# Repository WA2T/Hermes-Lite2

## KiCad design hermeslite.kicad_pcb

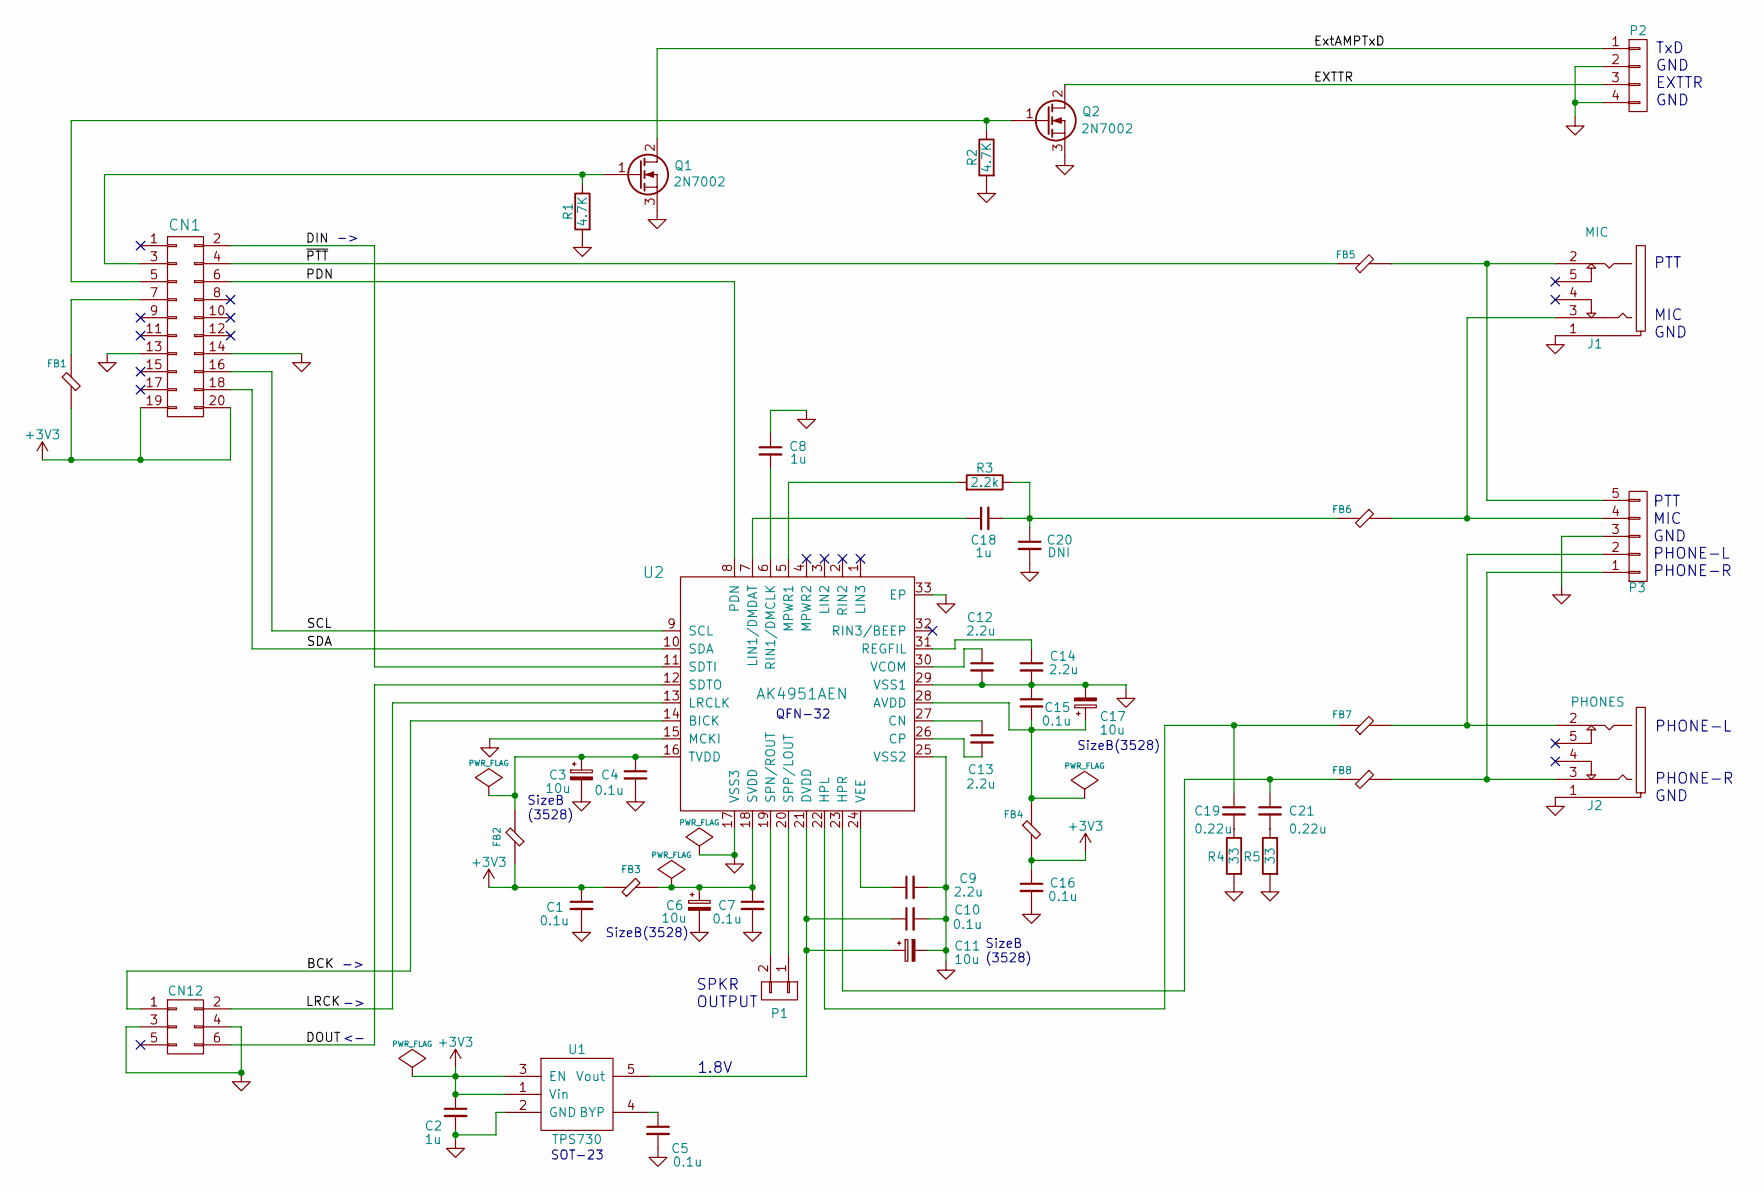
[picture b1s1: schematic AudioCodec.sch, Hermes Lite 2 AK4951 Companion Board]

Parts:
C1, C4, C5, C7, C10, C15, C16: 0.1u; SMD-0603
C2, C8, C18: 1u; SMD-0603
C3, C6, C11, C17: 10u; SMD-1206
C9, C12, C13, C14: 2.2u; SMD-0603
C19, C21: 0.22u; SMD-0603
C20: DNI; SMD-0603
CN1: IO20; 10x2
CN12: CONN_02X03; 3x2
FB1, FB2, FB3, FB4, FB5, FB6, FB7, FB8: FB; SMD-0603
J1: MIC; STEREO
J2: PHONES; STEREO
P1: CONN_01X02; 2x1
P2: CONN_01X04; 4x1
P3: CONN_01X05; 5x1
Q1, Q2: 2N7002; SOT23_2N7002
R1, R2: 4.7K; SMD-0603
R3: 2.2k; SMD-0603
R4, R5: 33; SMD-0603
U1: TPS730; SOT23
U2: AK4951AEN; QFN-32-1EP_4x4mm_Pitch0.4mm_Handsoldering

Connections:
+3V3: C1.1, C2.1, C16.1, CN1.19, CN1.20, FB1.1, FB2.2, FB3.2, FB4.1, U1.1 (Vin), U1.3 (EN)
/AudioCodec/BCK: CN12.1, U2.14 (BICK)
/AudioCodec/DIN: CN1.2, U2.11 (SDTI)
/AudioCodec/DOUT: CN12.6, U2.12 (SDTO)
/AudioCodec/EXTTR: P2.3, Q2.2 (D)
/AudioCodec/ExtAMPTxD: P2.1, Q1.2 (D)
/AudioCodec/LRCK: CN12.2, U2.13 (LRCLK)
/AudioCodec/PDN: CN1.6, U2.8 (PDN)
/AudioCodec/SCL: CN1.16, U2.9 (SCL)
/AudioCodec/SDA: CN1.18, U2.10 (SDA)
/AudioCodec/~PTT: CN1.4, FB5.2
GND: C1.2, C2.2, C3.2, C4.2, C5.2, C6.2, C7.2, C8.1, C9.2, C10.2, C11.2, C12.2, C14.2, C15.1, C16.2, C17.2, C20.2, CN1.13, CN1.14, CN12.3, CN12.4, J1.1, J2.1, P2.2, P2.4, P3.3, Q1.3 (S), Q2.3 (S), R1.2, R2.2, R4.2, R5.2, U1.2 (GND), U2.15 (MCKI), U2.17 (VSS3), U2.25 (VSS2), U2.29 (VSS1), U2.33 (EP)
unnamed: C3.1, C4.1, FB2.1, U2.16 (TVDD)
unnamed: C5.1, U1.4 (BYP)
unnamed: C6.1, C7.1, FB3.1, U2.18 (SVDD)
unnamed: C8.2, U2.6 (RIN1/DMCLK)
unnamed: C9.1, U2.24 (VEE)
unnamed: C10.1, C11.1, U1.5 (Vout), U2.21 (DVDD)
unnamed: C12.1, U2.30 (VCOM)
unnamed: C13.1, U2.27 (CN)
unnamed: C13.2, U2.26 (CP)
unnamed: C14.1, U2.31 (REGFIL)
unnamed: C15.2, C17.1, FB4.2, U2.28 (AVDD)
unnamed: C18.1, U2.7 (LIN1/DMDAT)
unnamed: C18.2, C20.1, FB6.1, R3.1
unnamed: C19.1, FB7.2, U2.22 (HPL)
unnamed: C19.2, R4.1
unnamed: C21.1, FB8.1, U2.23 (HPR)
unnamed: C21.2, R5.1
unnamed: CN1.3, Q1.1 (G), R1.1
unnamed: CN1.5, Q2.1 (G), R2.1
unnamed: CN1.7, FB1.2
unnamed: FB5.1, J1.2, P3.5
unnamed: FB6.2, J1.3, P3.4
unnamed: FB7.1, J2.2, P3.2
unnamed: FB8.2, J2.3, P3.1
unnamed: P1.1, U2.20 (SPP/LOUT)
unnamed: P1.2, U2.19 (SPN/ROUT)
unnamed: R3.2, U2.5 (MPWR1)

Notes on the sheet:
SPKR OUTPUT
PHONE-L PHONE-R GND
1.8V
PTT MIC GND PHONE-L PHONE-R
TxD GND EXTTR GND
SizeB (3528)
SizeB(3528)
SOT-23
QFN-32
PTT MIC GND

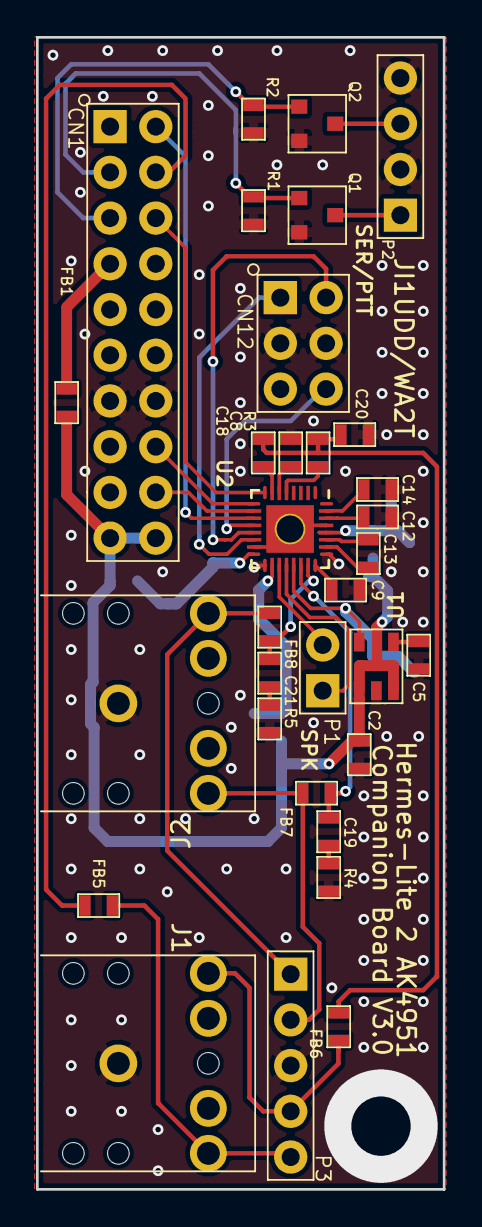
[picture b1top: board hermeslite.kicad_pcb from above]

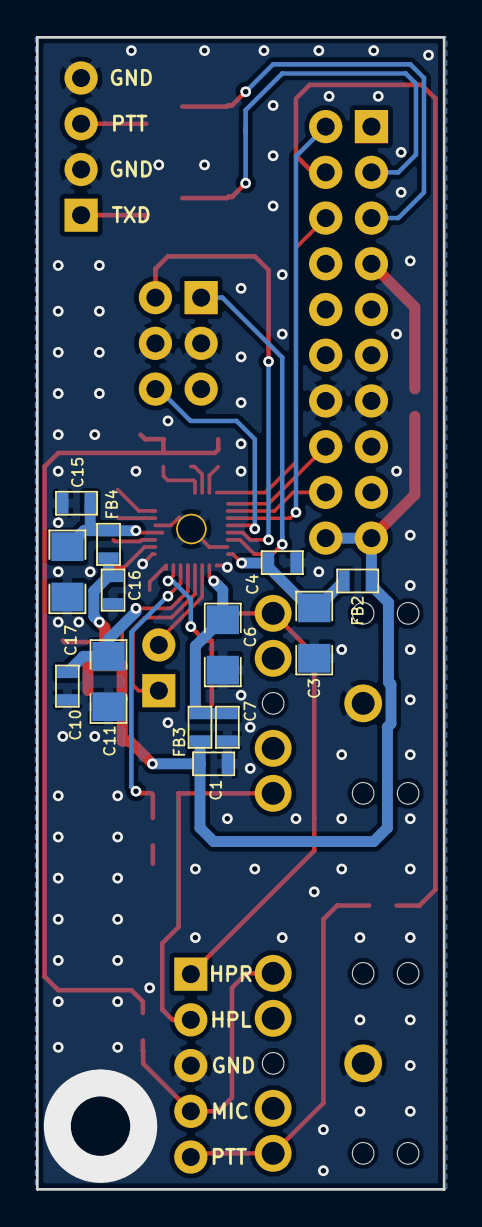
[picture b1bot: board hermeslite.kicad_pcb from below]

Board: 4 copper layers, 22.6 x 64.0 mm, 45 parts (13 on the bottom side), 39 nets.

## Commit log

2019-07-31 Create New_Codec_Board
2019-08-19 Add files via upload
    Converted to KiCad V5.0.2.
2019-09-18 Add files via upload
    Added paste mask files
2019-09-19 Create Build Info
2019-10-04 Add files via upload
    J1, J2 PJ-307 Jack Modification
2019-10-07 Add files via upload
    Added Taka-san's HR-50 Serial Interface document.
2019-10-18 Add files via upload
    Alternate mic jack fix.
